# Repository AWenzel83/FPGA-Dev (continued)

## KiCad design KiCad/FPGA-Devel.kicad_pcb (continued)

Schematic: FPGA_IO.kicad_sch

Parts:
C601, C602, C603, C604, C608, C609, C610, C611: 470n; C_0402_1005Metric
C605, C607: 4u7; C_0603_1608Metric
C606: 47u; C_1206_3216Metric
R601: 1k; R_0402_1005Metric
R602, R603, R604, R605, R606: 100; R_0402_1005Metric
U502: XC7S50FTGB196; Xilinx_FTGB196

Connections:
+3.3V: C601.1, C602.1, C603.1, C604.1, C605.1, C606.1, C607.1, C608.1, C609.1, C610.1, C611.1, R601.2, U502.G2 (VCCO_34), U502.G13 (VCCO_14), U502.K2 (VCCO_34), U502.K13 (VCCO_14), U502.N2 (VCCO_34), U502.N13 (VCCO_14); also elsewhere on the board
/ADC/ADC.FB_out0: U502.A2 (IO_L3N_T0_DQS_34); also elsewhere on the board
/ADC/ADC.FB_out1: U502.A4 (IO_L2P_T0_34); also elsewhere on the board
/ADC/ADC.SD_in0: U502.B3 (IO_L3P_T0_DQS_34); also elsewhere on the board
/ADC/ADC.SD_in1: U502.A3 (IO_L2N_T0_34); also elsewhere on the board
/Connectors/PMOD.A1: U502.A12 (IO_L4P_T0_D04_14); also elsewhere on the board
/Connectors/PMOD.A2: U502.B13 (IO_L5P_T0_D06_14); also elsewhere on the board
/Connectors/PMOD.A3: U502.D14 (IO_L11P_T1_SRCC_14); also elsewhere on the board
/Connectors/PMOD.A4: U502.D12 (IO_L8P_T1_D11_14); also elsewhere on the board
/Connectors/PMOD.A5: U502.A13 (IO_L4N_T0_D05_14); also elsewhere on the board
/Connectors/PMOD.A6: U502.B14 (IO_L5N_T0_D07_14); also elsewhere on the board
/Connectors/PMOD.A7: U502.C14 (IO_L11N_T1_SRCC_14); also elsewhere on the board
/Connectors/PMOD.A8: U502.D13 (IO_L8N_T1_D12_14); also elsewhere on the board
/Connectors/PMOD.B1: U502.F13 (IO_L10P_T1_D14_14); also elsewhere on the board
/Connectors/PMOD.B2: U502.G14 (IO_L9P_T1_DQS_14); also elsewhere on the board
/Connectors/PMOD.B3: U502.H13 (IO_L14P_T2_SRCC_14); also elsewhere on the board
/Connectors/PMOD.B4: U502.J13 (IO_L18P_T2_A12_D28_14); also elsewhere on the board
/Connectors/PMOD.B5: U502.E13 (IO_L10N_T1_D15_14); also elsewhere on the board
/Connectors/PMOD.B6: U502.F14 (IO_L9N_T1_DQS_D13_14); also elsewhere on the board
/Connectors/PMOD.B7: U502.H14 (IO_L14N_T2_SRCC_14); also elsewhere on the board
/Connectors/PMOD.B8: U502.J14 (IO_L18N_T2_A11_D27_14); also elsewhere on the board
/Connectors/PMOD.C1: U502.M11 (IO_L20P_T3_A08_D24_14); also elsewhere on the board
/Connectors/PMOD.C2: U502.N14 (IO_L21P_T3_DQS_14); also elsewhere on the board
/Connectors/PMOD.C3: U502.P12 (IO_L22P_T3_A05_D21_14); also elsewhere on the board
/Connectors/PMOD.C4: U502.N10 (IO_L23P_T3_A03_D19_14); also elsewhere on the board
/Connectors/PMOD.C5: U502.M12 (IO_L20N_T3_A07_D23_14); also elsewhere on the board
/Connectors/PMOD.C6: U502.M14 (IO_L21N_T3_DQS_A06_D22_14); also elsewhere on the board
/Connectors/PMOD.C7: U502.P13 (IO_L22N_T3_A04_D20_14); also elsewhere on the board
/Connectors/PMOD.C8: U502.N11 (IO_L23N_T3_A02_D18_14); also elsewhere on the board
/Connectors/USB.DM: U502.L14 (IO_L15N_T2_DQS_DOUT_CSO_B_14); also elsewhere on the board
/Connectors/USB.DP: U502.M13 (IO_L15P_T2_DQS_RDWR_B_14); also elsewhere on the board
/Connectors/USB.PUR: U502.L13 (IO_L16N_T2_A15_D31_14); also elsewhere on the board
/FT2232/UART.CTS: U502.C1 (IO_L11N_T1_SRCC_34); also elsewhere on the board
/FT2232/UART.RTS: U502.D2 (IO_L10N_T1_34); also elsewhere on the board
/FT2232/UART.RX: U502.E2 (IO_L10P_T1_34); also elsewhere on the board
/FT2232/UART.TX: U502.D1 (IO_L11P_T1_SRCC_34); also elsewhere on the board
/IO/Btn.A: U502.P10 (IO_L24P_T3_A01_D17_14); also elsewhere on the board
/IO/Btn.B: U502.P11 (IO_L24N_T3_A00_D16_14); also elsewhere on the board
/IO/Btn.C: U502.A5 (IO_L4N_T0_34); also elsewhere on the board
/IO/Btn.D: U502.B1 (IO_L5N_T0_34); also elsewhere on the board
/IO/Btn.L: U502.D3 (IO_L1P_T0_34); also elsewhere on the board
/IO/Btn.R: U502.B2 (IO_L5P_T0_34); also elsewhere on the board
/IO/Btn.U: U502.C3 (IO_L1N_T0_34); also elsewhere on the board
/IO/Btn.ZL: U502.M5 (IO_L23P_T3_34); also elsewhere on the board
/IO/Btn.ZR: U502.L5 (IO_25_34); also elsewhere on the board
/IO/Display.A: U502.J11 (IO_L17P_T2_A14_D30_14); also elsewhere on the board
/IO/Display.AN1: U502.C12 (IO_L6N_T0_D08_VREF_14); also elsewhere on the board
/IO/Display.AN2: U502.E12 (IO_L7N_T1_D10_14); also elsewhere on the board
/IO/Display.AN3: U502.J12 (IO_L17N_T2_A13_D29_14); also elsewhere on the board
/IO/Display.AN4: U502.M10 (IO_25_14); also elsewhere on the board
/IO/Display.AN5: U502.H11 (IO_L13P_T2_MRCC_14); also elsewhere on the board
/IO/Display.B: U502.F11 (IO_L12N_T1_MRCC_14); also elsewhere on the board
/IO/Display.C: U502.L12 (IO_L16P_T2_CSI_B_14); also elsewhere on the board
/IO/Display.D: U502.F12 (IO_L7P_T1_D09_14); also elsewhere on the board
/IO/Display.DP: U502.K11 (IO_L19P_T3_A10_D26_14); also elsewhere on the board
/IO/Display.E: U502.H12 (IO_L13N_T2_MRCC_14); also elsewhere on the board
/IO/Display.F: U502.K12 (IO_L19N_T3_A09_D25_VREF_14); also elsewhere on the board
/IO/Display.G: U502.G11 (IO_L12P_T1_MRCC_14); also elsewhere on the board
/IO/LED0: U502.J1 (IO_L15N_T2_DQS_34); also elsewhere on the board
/IO/LED1: U502.J2 (IO_L15P_T2_DQS_34); also elsewhere on the board
/IO/LED2: U502.K3 (IO_L16N_T2_34); also elsewhere on the board
/IO/LED3: U502.L3 (IO_L22P_T3_34); also elsewhere on the board
/IO/LED4: U502.M3 (IO_L19P_T3_34); also elsewhere on the board
/IO/LED5: U502.K4 (IO_L16P_T2_34); also elsewhere on the board
/IO/LED6: U502.P2 (IO_L20P_T3_34); also elsewhere on the board
/IO/LED7: U502.P3 (IO_L21N_T3_DQS_34); also elsewhere on the board
/IO/MISC.CLK: U502.G4 (IO_L12P_T1_MRCC_34); also elsewhere on the board
/IO/MISC.RST: U502.H1 (IO_L14N_T2_SRCC_34); also elsewhere on the board
/IO/Rotary.A: U502.H2 (IO_L14P_T2_SRCC_34); also elsewhere on the board
/IO/Rotary.B: U502.G1 (IO_L9P_T1_DQS_34); also elsewhere on the board
/IO/Rotary.S: U502.F1 (IO_L9N_T1_DQS_34); also elsewhere on the board
/IO/SW.A0: U502.D4 (IO_L7N_T1_34); also elsewhere on the board
/IO/SW.A1: U502.C5 (IO_L6P_T0_34); also elsewhere on the board
/IO/SW.A2: U502.C4 (IO_L6N_T0_VREF_34); also elsewhere on the board
/IO/SW.A3: U502.E4 (IO_L7P_T1_34); also elsewhere on the board
/IO/SW.B0: U502.P4 (IO_L21P_T3_DQS_34); also elsewhere on the board
/IO/SW.B1: U502.M4 (IO_L23N_T3_34); also elsewhere on the board
/IO/SW.B2: U502.N4 (IO_L24N_T3_34); also elsewhere on the board
/IO/SW.B3: U502.P5 (IO_L24P_T3_34); also elsewhere on the board
/Memory/SPI_Mem.CS0: U502.C11 (IO_L6P_T0_FCS_B_14); also elsewhere on the board
/Memory/SPI_Mem.CS1: U502.A10 (IO_L3N_T0_DQS_EMCCLK_14); also elsewhere on the board
/Memory/SPI_Mem.HOLD: R606.1; also elsewhere on the board
/Memory/SPI_Mem.MISO: R604.1; also elsewhere on the board
/Memory/SPI_Mem.MOSI: R603.1; also elsewhere on the board
/Memory/SPI_Mem.SCLK: R602.1; also elsewhere on the board
/Memory/SPI_Mem.WP: R605.1; also elsewhere on the board
/Memory/μSD.CS: U502.L1 (IO_L18N_T2_34); also elsewhere on the board
/Memory/μSD.Detect: U502.N1 (IO_L20N_T3_34); also elsewhere on the board
/Memory/μSD.MISO: U502.M2 (IO_L19N_T3_VREF_34); also elsewhere on the board
/Memory/μSD.MOSI: U502.L2 (IO_L22N_T3_34); also elsewhere on the board
/Memory/μSD.SCLK: U502.M1 (IO_L18P_T2_34); also elsewhere on the board
GND: C601.2, C602.2, C603.2, C604.2, C605.2, C606.2, C607.2, C608.2, C609.2, C610.2, C611.2; also elsewhere on the board
unnamed: R602.2, U502.E11 (IO_0_14)
unnamed: R604.2, U502.B12 (IO_L1N_T0_D01_DIN_14)
unnamed: R603.2, U502.B11 (IO_L1P_T0_D00_MOSI_14)
unnamed: R606.2, U502.C10 (IO_L2N_T0_D03_14)
unnamed: R605.2, U502.D10 (IO_L2P_T0_D02_14)
unnamed: R601.1, U502.B10 (IO_L3P_T0_DQS_PUDC_B_14)

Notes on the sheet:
I identify as a small BUS-entry just copy & paste as needed

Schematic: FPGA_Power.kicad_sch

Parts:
C701, C702, C703, C704, C705, C712, C715, C716, C717: 470n; C_0402_1005Metric
C706, C707, C708, C711, C714: 4u7; C_0603_1608Metric
C709: 100u; C_1206_3216Metric
C710, C713: 47u; C_1206_3216Metric
U502: XC7S50FTGB196; Xilinx_FTGB196

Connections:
+1V0: C701.1, C702.1, C703.1, C704.1, C705.1, C706.1, C707.1, C708.1, C709.1, C710.1, C711.1, C712.1, U502.D6 (VCCINT), U502.D8 (VCCINT), U502.E5 (VCCBRAM), U502.E7 (VCCINT), U502.E9 (VCCINT), U502.F6 (VCCINT), U502.G5 (VCCBRAM), U502.G9 (VCCINT), U502.H6 (VCCINT), U502.J5 (VCCBRAM), U502.J9 (VCCINT), U502.K6 (VCCINT), U502.K8 (VCCINT); also elsewhere on the board
+1V8: C713.1, C714.1, C715.1, C716.1, C717.1, U502.F8 (VCCADC_0), U502.F10 (VCCAUX), U502.H10 (VCCAUX), U502.K10 (VCCAUX), U502.L9 (VCCAUX); also elsewhere on the board
GND: C701.2, C702.2, C703.2, C704.2, C705.2, C706.2, C707.2, C708.2, C709.2, C710.2, C711.2, C712.2, C713.2, C714.2, C715.2, C716.2, C717.2, U502.A1 (GND), U502.A6 (GND), U502.A9 (GND), U502.A11 (GND), U502.A14 (GND), U502.B4 (GND), U502.B7 (GND), U502.B8 (VCCBATT_0), U502.B9 (GND), U502.C2 (GND), U502.C6 (GND), U502.C7 (GND), U502.C8 (GND), U502.C9 (GND), U502.C13 (GND), U502.D5 (GND), U502.D7 (GND), U502.D9 (GND), U502.D11 (GND), U502.E1 (GND), U502.E3 (GND), U502.E6 (GND), U502.E8 (GND), U502.E10 (GND), U502.E14 (GND), U502.F5 (GND), U502.F7 (GNDADC_0), U502.F9 (GND), U502.G3 (GND), U502.G6 (GND), U502.G10 (GND), U502.G12 (GND), U502.H5 (GND), U502.H9 (GND), U502.J6 (GND), U502.J10 (GND), U502.K1 (GND), U502.K5 (GND), U502.K7 (GND), U502.K9 (GND), U502.K14 (GND), U502.L4 (GND), U502.L6 (GND), U502.L8 (GND), U502.L10 (GND), U502.L11 (GND), U502.N3 (GND), U502.N5 (GND), U502.N9 (GND), U502.N12 (GND), U502.P1 (GND), U502.P14 (GND); also elsewhere on the board

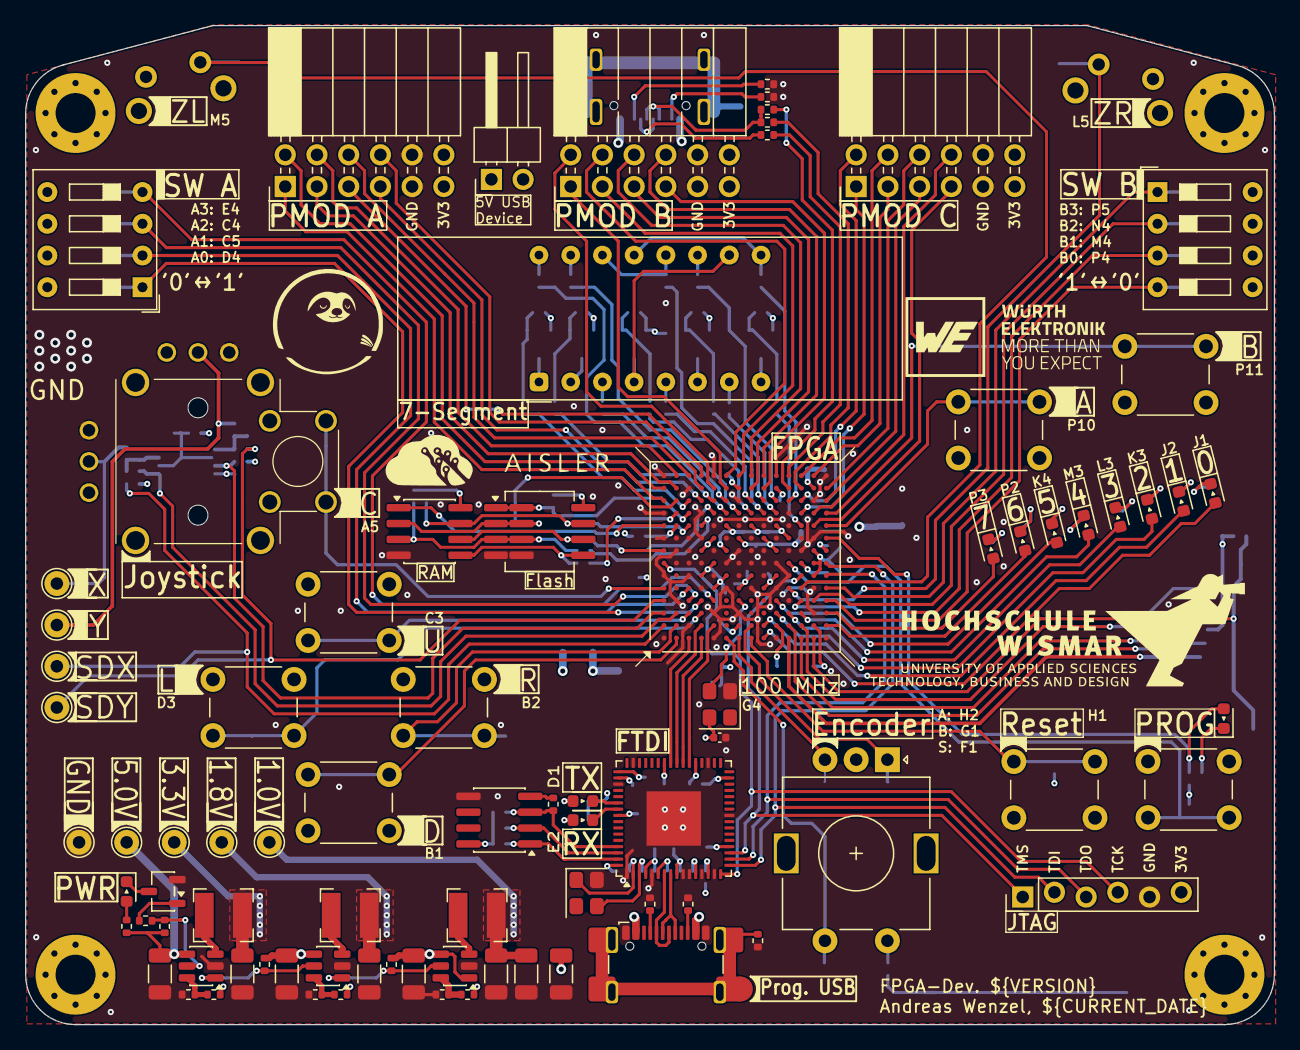
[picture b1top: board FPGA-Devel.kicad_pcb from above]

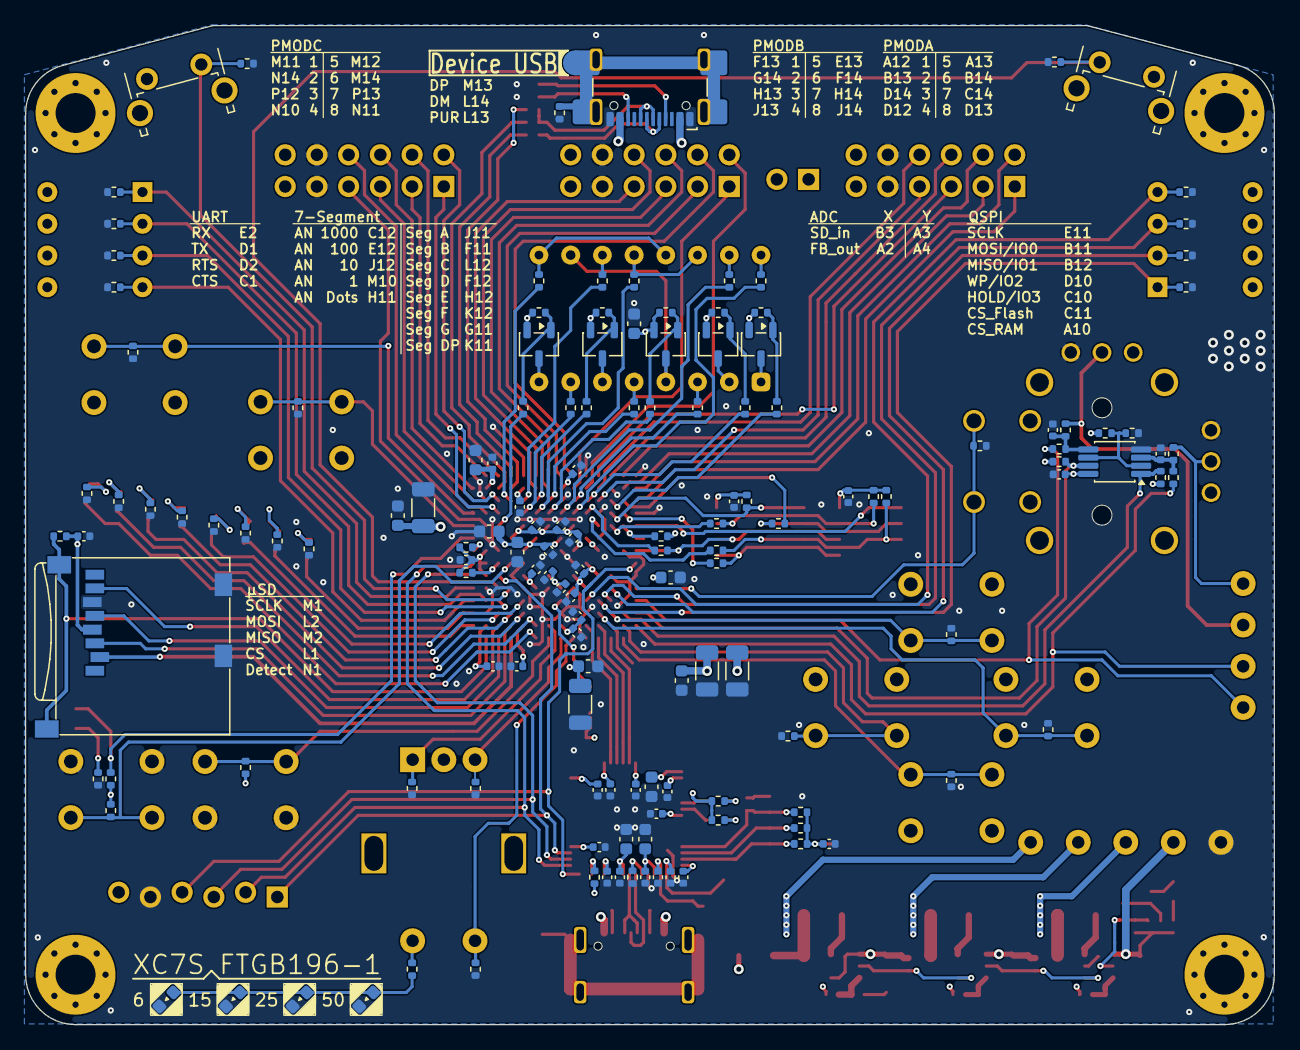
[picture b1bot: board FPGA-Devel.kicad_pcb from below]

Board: 4 copper layers, 100.0 x 80.0 mm, 231 parts (144 on the bottom side), 178 nets.

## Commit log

2025-10-09 KiCad-Files added
2025-10-22 Combo-Footprint für Flash
2025-10-22 Combo-Footprint für Flash (auch im Schematic)
2025-10-28 kleine Layout-Anpassungen, Silkscreen korrigiert
2025-10-29 mehr kleine Layout-Anpassungen
2025-11-12 kleine Anpassungen im Silkscreen
2025-11-18 kleine Anpassungen im Schaltplan
2025-11-19 replaced SAR-ADC with Sigma-Delta-Converter
2026-03-17 Vorberitung für micro-SD
2026-03-18 micro-SD hinzugefügt
2026-03-19 Pinout und Silkscreen angepasst
2026-03-24 Update auf KiCad 10
2026-03-24 Step-Files angepasst, Logo hinzugefügt
2026-03-24 Vergessen die Polygone neu zeichnen zu lassen...
2026-04-13 LEDs zur Visualisierung des ausgewählten FPGAs
2026-04-17 JTAG-Verbinder hinzugefügt
2026-05-18 minor touches
2026-06-23 Prepare v1.2
